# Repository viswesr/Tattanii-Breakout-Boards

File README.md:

Tattanii-Breakout-Boards
========================

Breakout Boards for Energy Micro EFM32 MCUs. These boards makes use of [EnergyMicro Eagle Library](https://github.com/viswesr/EnergyMicro-Eagle-Library)

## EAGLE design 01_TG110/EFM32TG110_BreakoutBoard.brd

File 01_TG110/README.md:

Tattanii-Breakout-Boards
========================

Tiny Gecko EFM32TG110 Breakout Boards. Released under CC-BY-SA 3.0 License.

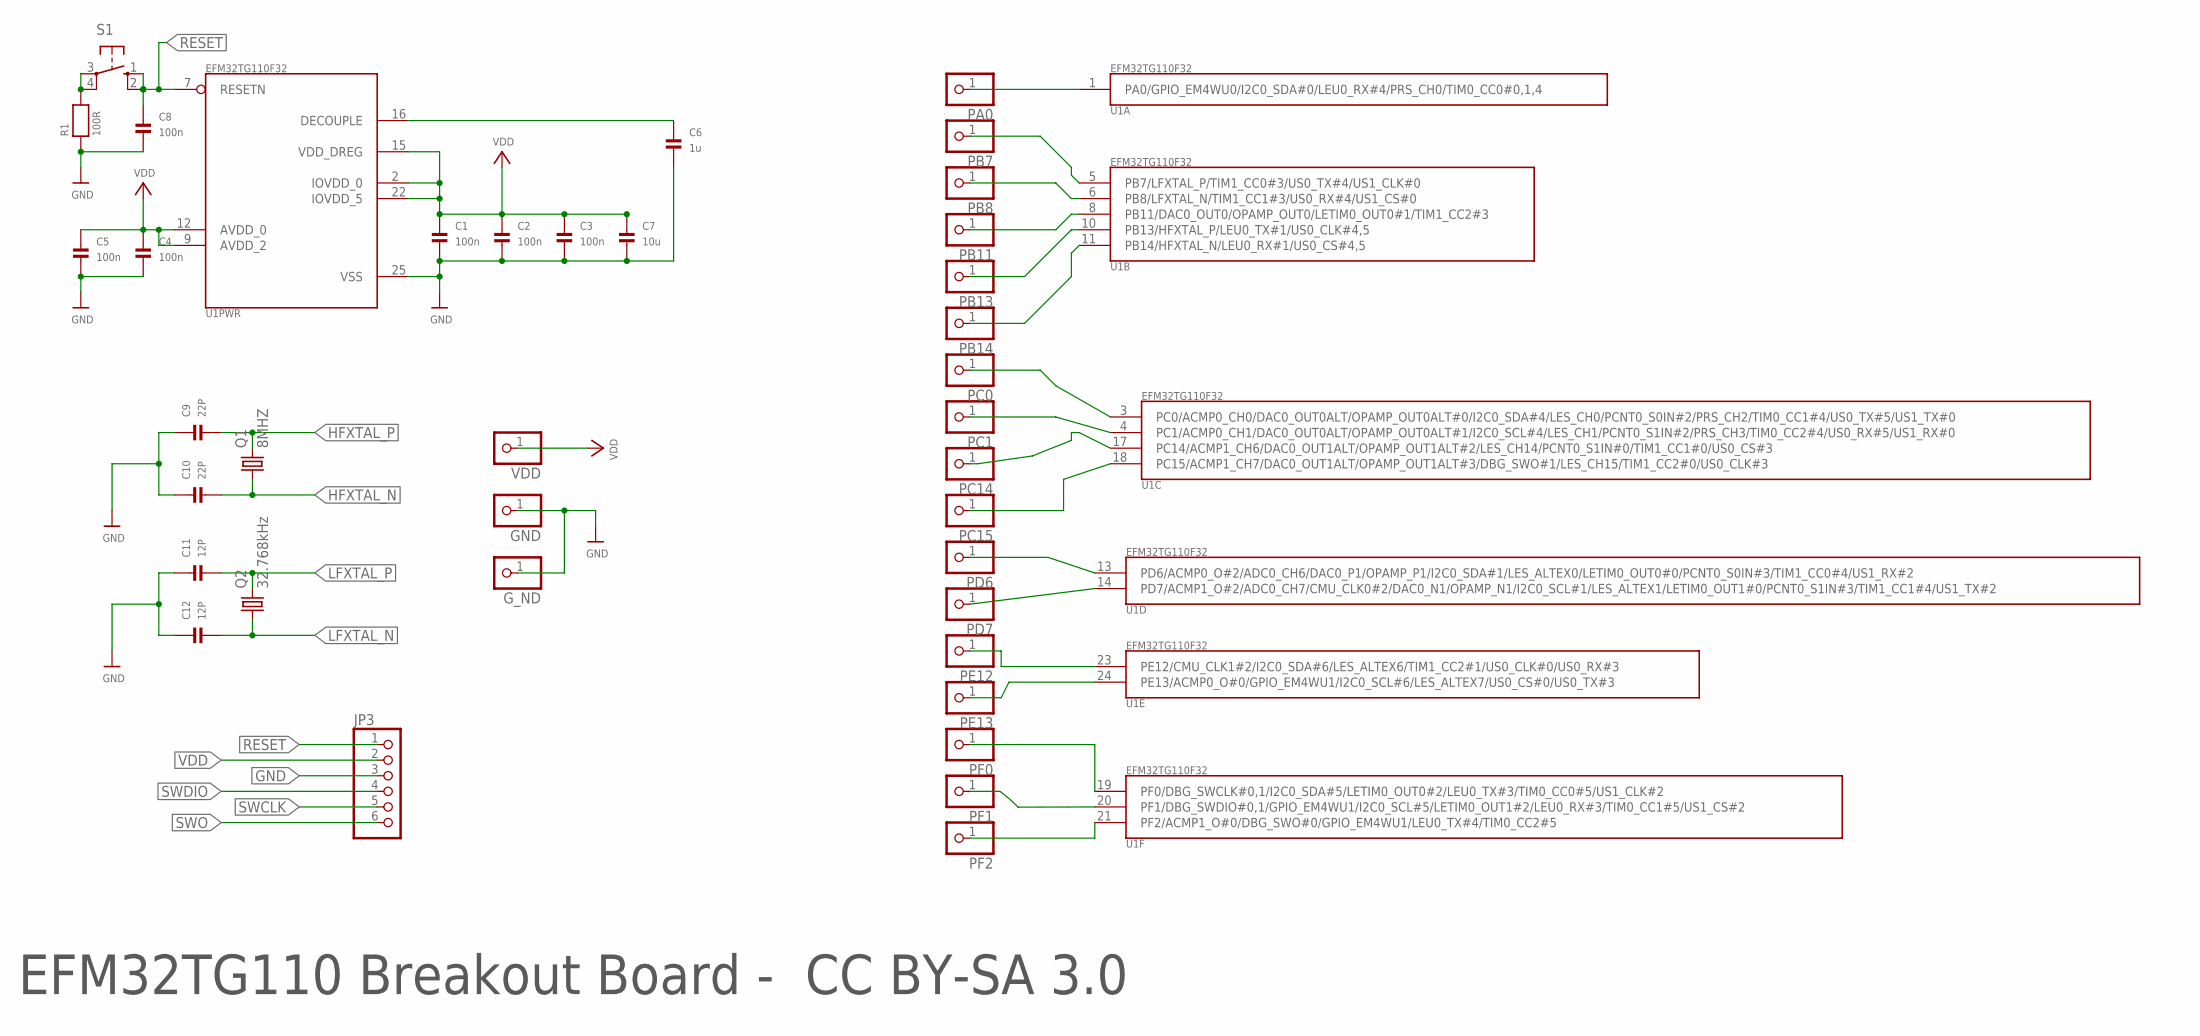
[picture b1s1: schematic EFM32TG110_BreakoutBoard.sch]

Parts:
C1, C2, C3, C4, C5, C8: 100n; 0603
C6: 1u; 0805
C7: 10u; 0805
C9, C10: 22P; 0603
C11, C12: 12P; 0603
GND: HEADER-1X1ROUND; 1X01_ROUND
G_ND: HEADER-1X1ROUND; 1X01_ROUND
JP3: HEADER-1X6; 1X06_OVAL
PA0: HEADER-1X1ROUND; 1X01_ROUND
PB7, PB8, PB11, PB13, PB14: HEADER-1X1ROUND; 1X01_ROUND
PC0, PC1, PC14, PC15: HEADER-1X1ROUND; 1X01_ROUND
PD6, PD7: HEADER-1X1ROUND; 1X01_ROUND
PE12, PE13: HEADER-1X1ROUND; 1X01_ROUND
PF0, PF1, PF2: HEADER-1X1ROUND; 1X01_ROUND
Q1: 8MHZ; HC49U70
Q2: 32.768kHz; TC38H
R1: 100R; 0603
S1: 10-XX; B3F-10XX
U1: EFM32TG110F32; QFN24
VDD: HEADER-1X1ROUND; 1X01_ROUND

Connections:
GND: C1.2, C2.2, C3.2, C4.2, C5.2, C6.2, C7.2, C8.2, C9.1, C10.1, C11.1, C12.1, GND.1, G_ND.1, JP3.3, R1.1, U1.25 (VSS)
HFXTAL_N: C10.2, PB14.1, Q1.1, U1.11 (PB14/HFXTAL_N/LEU0_RX#1/US0_CS#4,5)
HFXTAL_P: C9.2, PB13.1, Q1.2, U1.10 (PB13/HFXTAL_P/LEU0_TX#1/US0_CLK#4,5)
LFXTAL_N: C12.2, PB8.1, Q2.1, U1.6 (PB8/LFXTAL_N/TIM1_CC1#3/US0_RX#4/US1_CS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)
LFXTAL_P: C11.2, PB7.1, Q2.2, U1.5 (PB7/LFXTAL_P/TIM1_CC0#3/US0_TX#4/US1_CL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)
unnamed: PA0.1, U1.1 (PA0/GPIO_EM4WU0/I2C0_SDA#0/LEU0_RX#4/PR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)
unnamed: C6.1, U1.16 (DECOUPLE)
unnamed: PB11.1, U1.8 (PB11/DAC0_OUT0/OPAMP_OUT0/LETIM0_OUT0#1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)
unnamed: PC0.1, U1.3 (PC0/ACMP0_CH0/DAC0_OUT0ALT/OPAMP_OUT0AL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)
unnamed: PC1.1, U1.4 (PC1/ACMP0_CH1/DAC0_OUT0ALT/OPAMP_OUT0AL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)
unnamed: PC14.1, U1.17 (PC14/ACMP1_CH6/DAC0_OUT1ALT/OPAMP_OUT1A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)
unnamed: PC15.1, U1.18 (PC15/ACMP1_CH7/DAC0_OUT1ALT/OPAMP_OUT1A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)
unnamed: PD6.1, U1.13 (PD6/ACMP0_O#2/ADC0_CH6/DAC0_P1/OPAMP_P1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)
unnamed: PD7.1, U1.14 (PD7/ACMP1_O#2/ADC0_CH7/CMU_CLK0#2/DAC0_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)
unnamed: PE12.1, U1.23 (PE12/CMU_CLK1#2/I2C0_SDA#6/LES_ALTEX6/T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)
unnamed: PE13.1, U1.24 (PE13/ACMP0_O#0/GPIO_EM4WU1/I2C0_SCL#6/L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)
unnamed: R1.2, S1.3, S1.4 (P1)
RESET: C8.1, JP3.1, S1.1 (S), S1.2 (S1), U1.7 (RESETN)
SWCLK: JP3.5, PF0.1, U1.19 (PF0/DBG_SWCLK#0,1/I2C0_SDA#5/LETIM0_OUT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)
SWDIO: JP3.4, PF1.1, U1.20 (PF1/DBG_SWDIO#0,1/GPIO_EM4WU1/I2C0_SCL#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)
SWO: JP3.6, PF2.1, U1.21 (PF2/ACMP1_O#0/DBG_SWO#0/GPIO_EM4WU1/LEU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)
VDD: C1.1, C2.1, C3.1, C4.1, C5.1, C7.1, JP3.2, U1.2 (IOVDD_0), U1.9 (AVDD_2), U1.12 (AVDD_0), U1.15 (VDD_DREG), U1.22 (IOVDD_5), VDD.1

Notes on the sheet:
EFM32TG110 Breakout Board - CC BY-SA 3.0

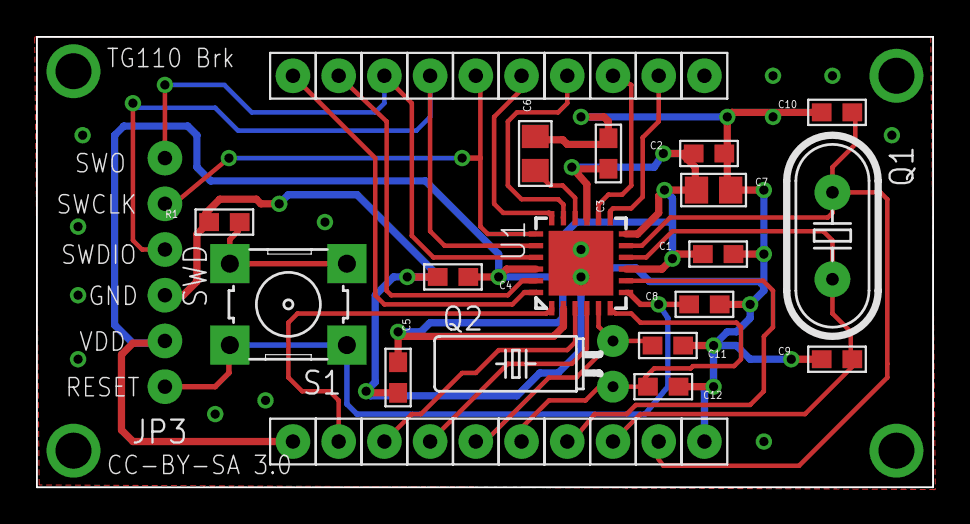
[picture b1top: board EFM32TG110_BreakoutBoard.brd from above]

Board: 2 copper layers, 49.8 x 25.0 mm, 38 parts (0 on the bottom side), 22 nets.

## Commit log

2012-10-01 Tiny Gecko TG110 Breakout Board added
2012-10-01 TG110BB screen-shot added
2012-10-01 Fix image url

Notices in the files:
parts and their libraries:
EnergyMicro: CC0 License
